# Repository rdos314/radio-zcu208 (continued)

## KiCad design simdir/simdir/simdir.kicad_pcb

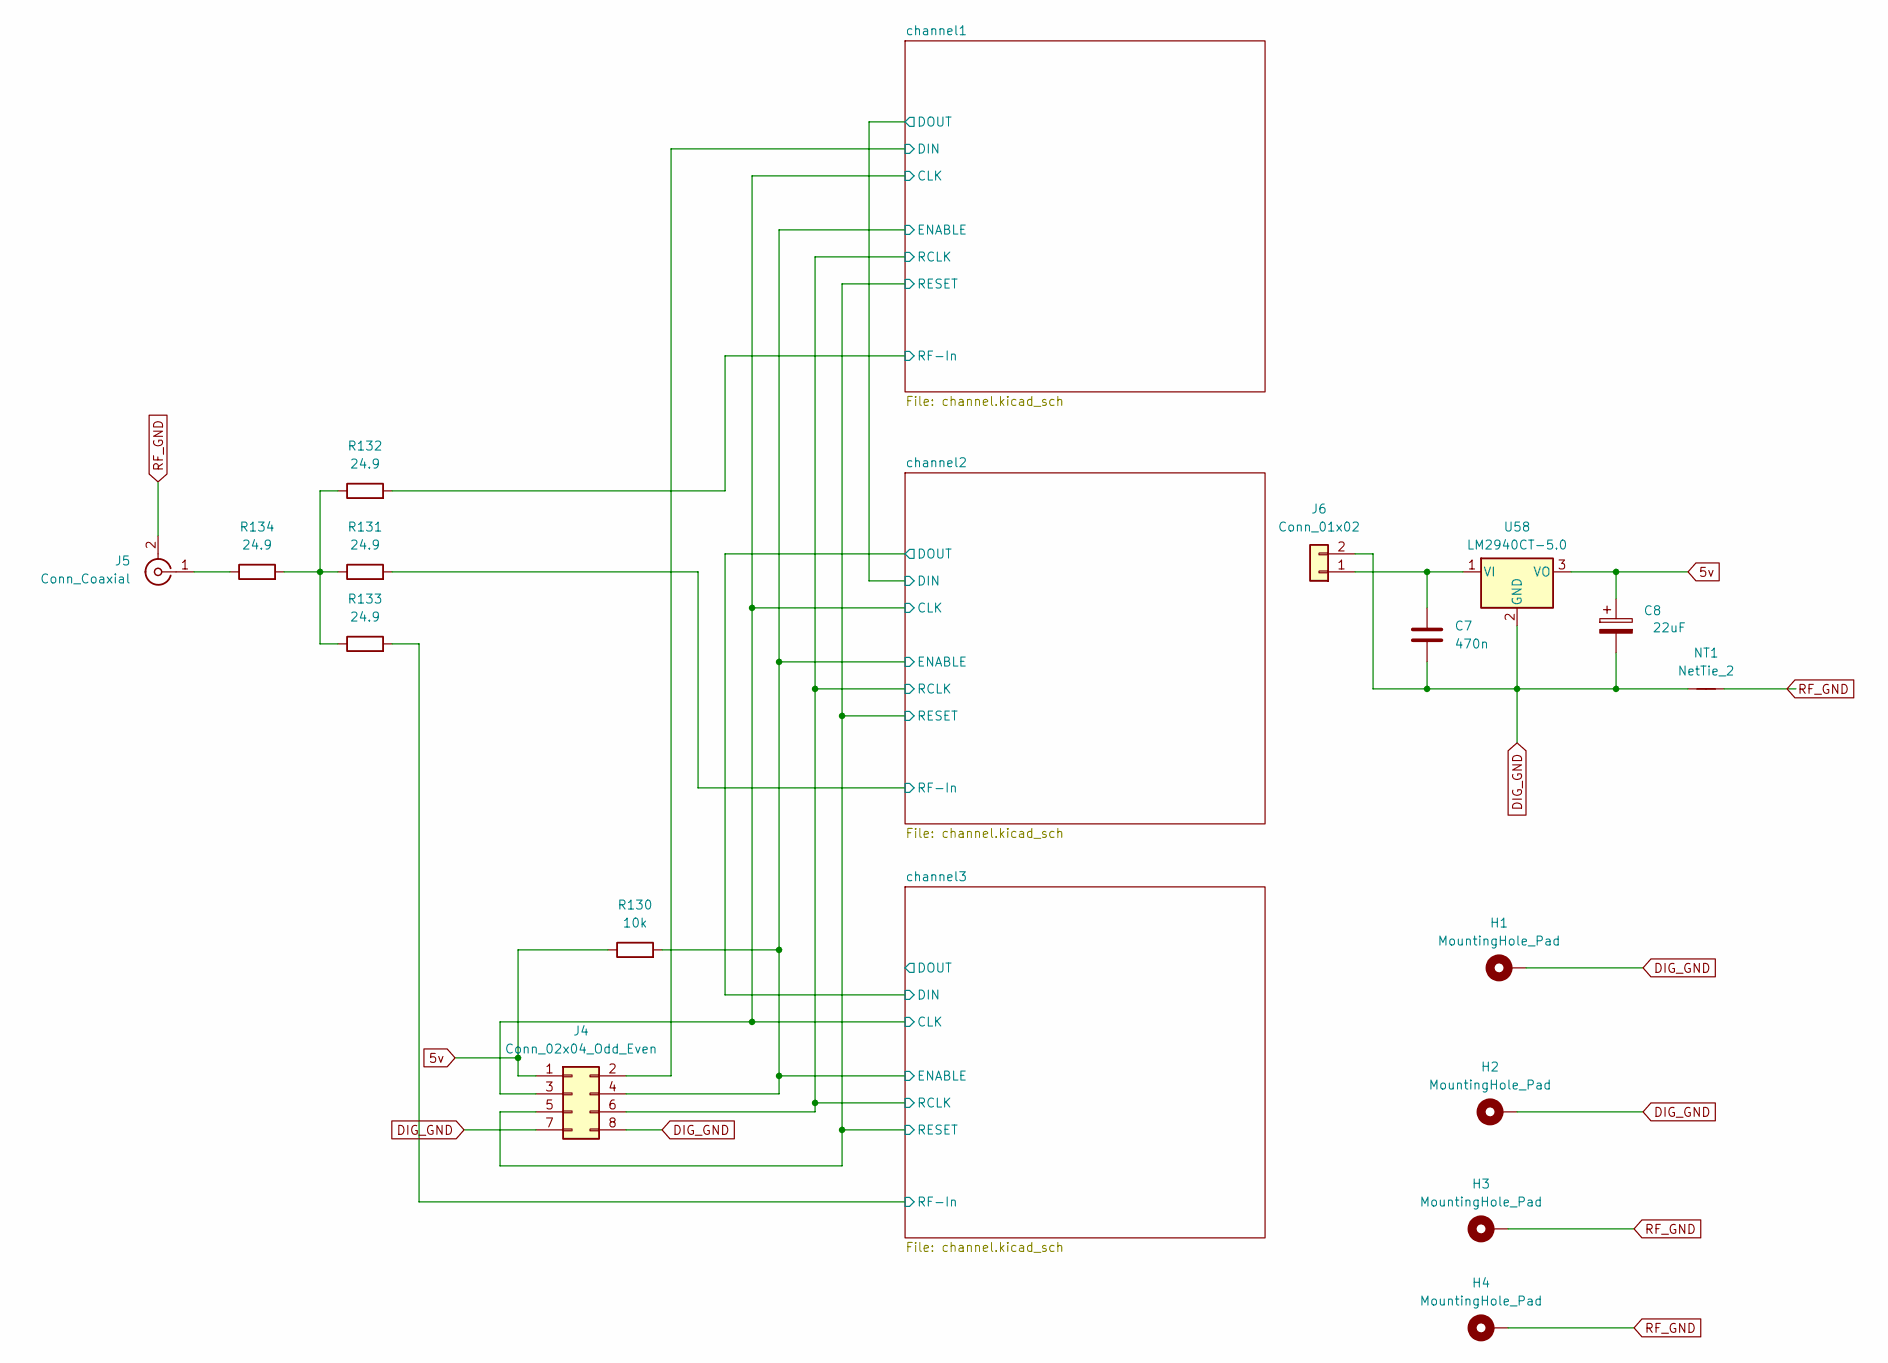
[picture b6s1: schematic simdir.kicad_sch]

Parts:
C7: 470n; C_Disc_D4.3mm_W1.9mm_P5.00mm
C8: 22uF; CP_Radial_D6.3mm_P2.50mm
H1, H2, H3, H4: MountingHole_Pad; MountingHole_4.3mm_M4_Pad_Via
J4: Conn_02x04_Odd_Even; PinHeader_2x04_P2.54mm_Vertical
J5: Conn_Coaxial; SMA_Amphenol_132289_EdgeMount
J6: Conn_01x02; PinHeader_1x02_P2.54mm_Vertical
NT1: NetTie_2; NetTie-2_THT_Pad1.0mm
R130: 10k; R_0805_2012Metric_Pad1.20x1.40mm_HandSolder
R131, R132, R133, R134: 24.9; R_0805_2012Metric_Pad1.20x1.40mm_HandSolder
U58: LM2940CT-5.0; TO-220-3_Horizontal_TabDown

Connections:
5v: C8.1, J4.1, R130.1, U58.3 (VO); also elsewhere on the board
/channel1/CLK: J4.3; also elsewhere on the board
/channel1/DIN: J4.2; also elsewhere on the board
/channel1/ENABLE: J4.4, R130.2; also elsewhere on the board
/channel1/RCLK: J4.6; also elsewhere on the board
/channel1/RESET: J4.5; also elsewhere on the board
/channel1/RF-In: R132.2; also elsewhere on the board
/channel2/RF-In: R131.2; also elsewhere on the board
/channel3/RF-In: R133.2; also elsewhere on the board
DIG_GND: C7.2, C8.2, H1.1 (1_1), H2.1 (1_1), J4.7, J4.8, J6.2, NT1.1, U58.2 (GND); also elsewhere on the board
unnamed: J5.1 (In), R134.1
unnamed: C7.1, J6.1, U58.1 (VI)
unnamed: R131.1, R132.1, R133.1, R134.2
RF_GND: H3.1 (1_1), H4.1 (1_1), J5.2 (Ext), NT1.2; also elsewhere on the board

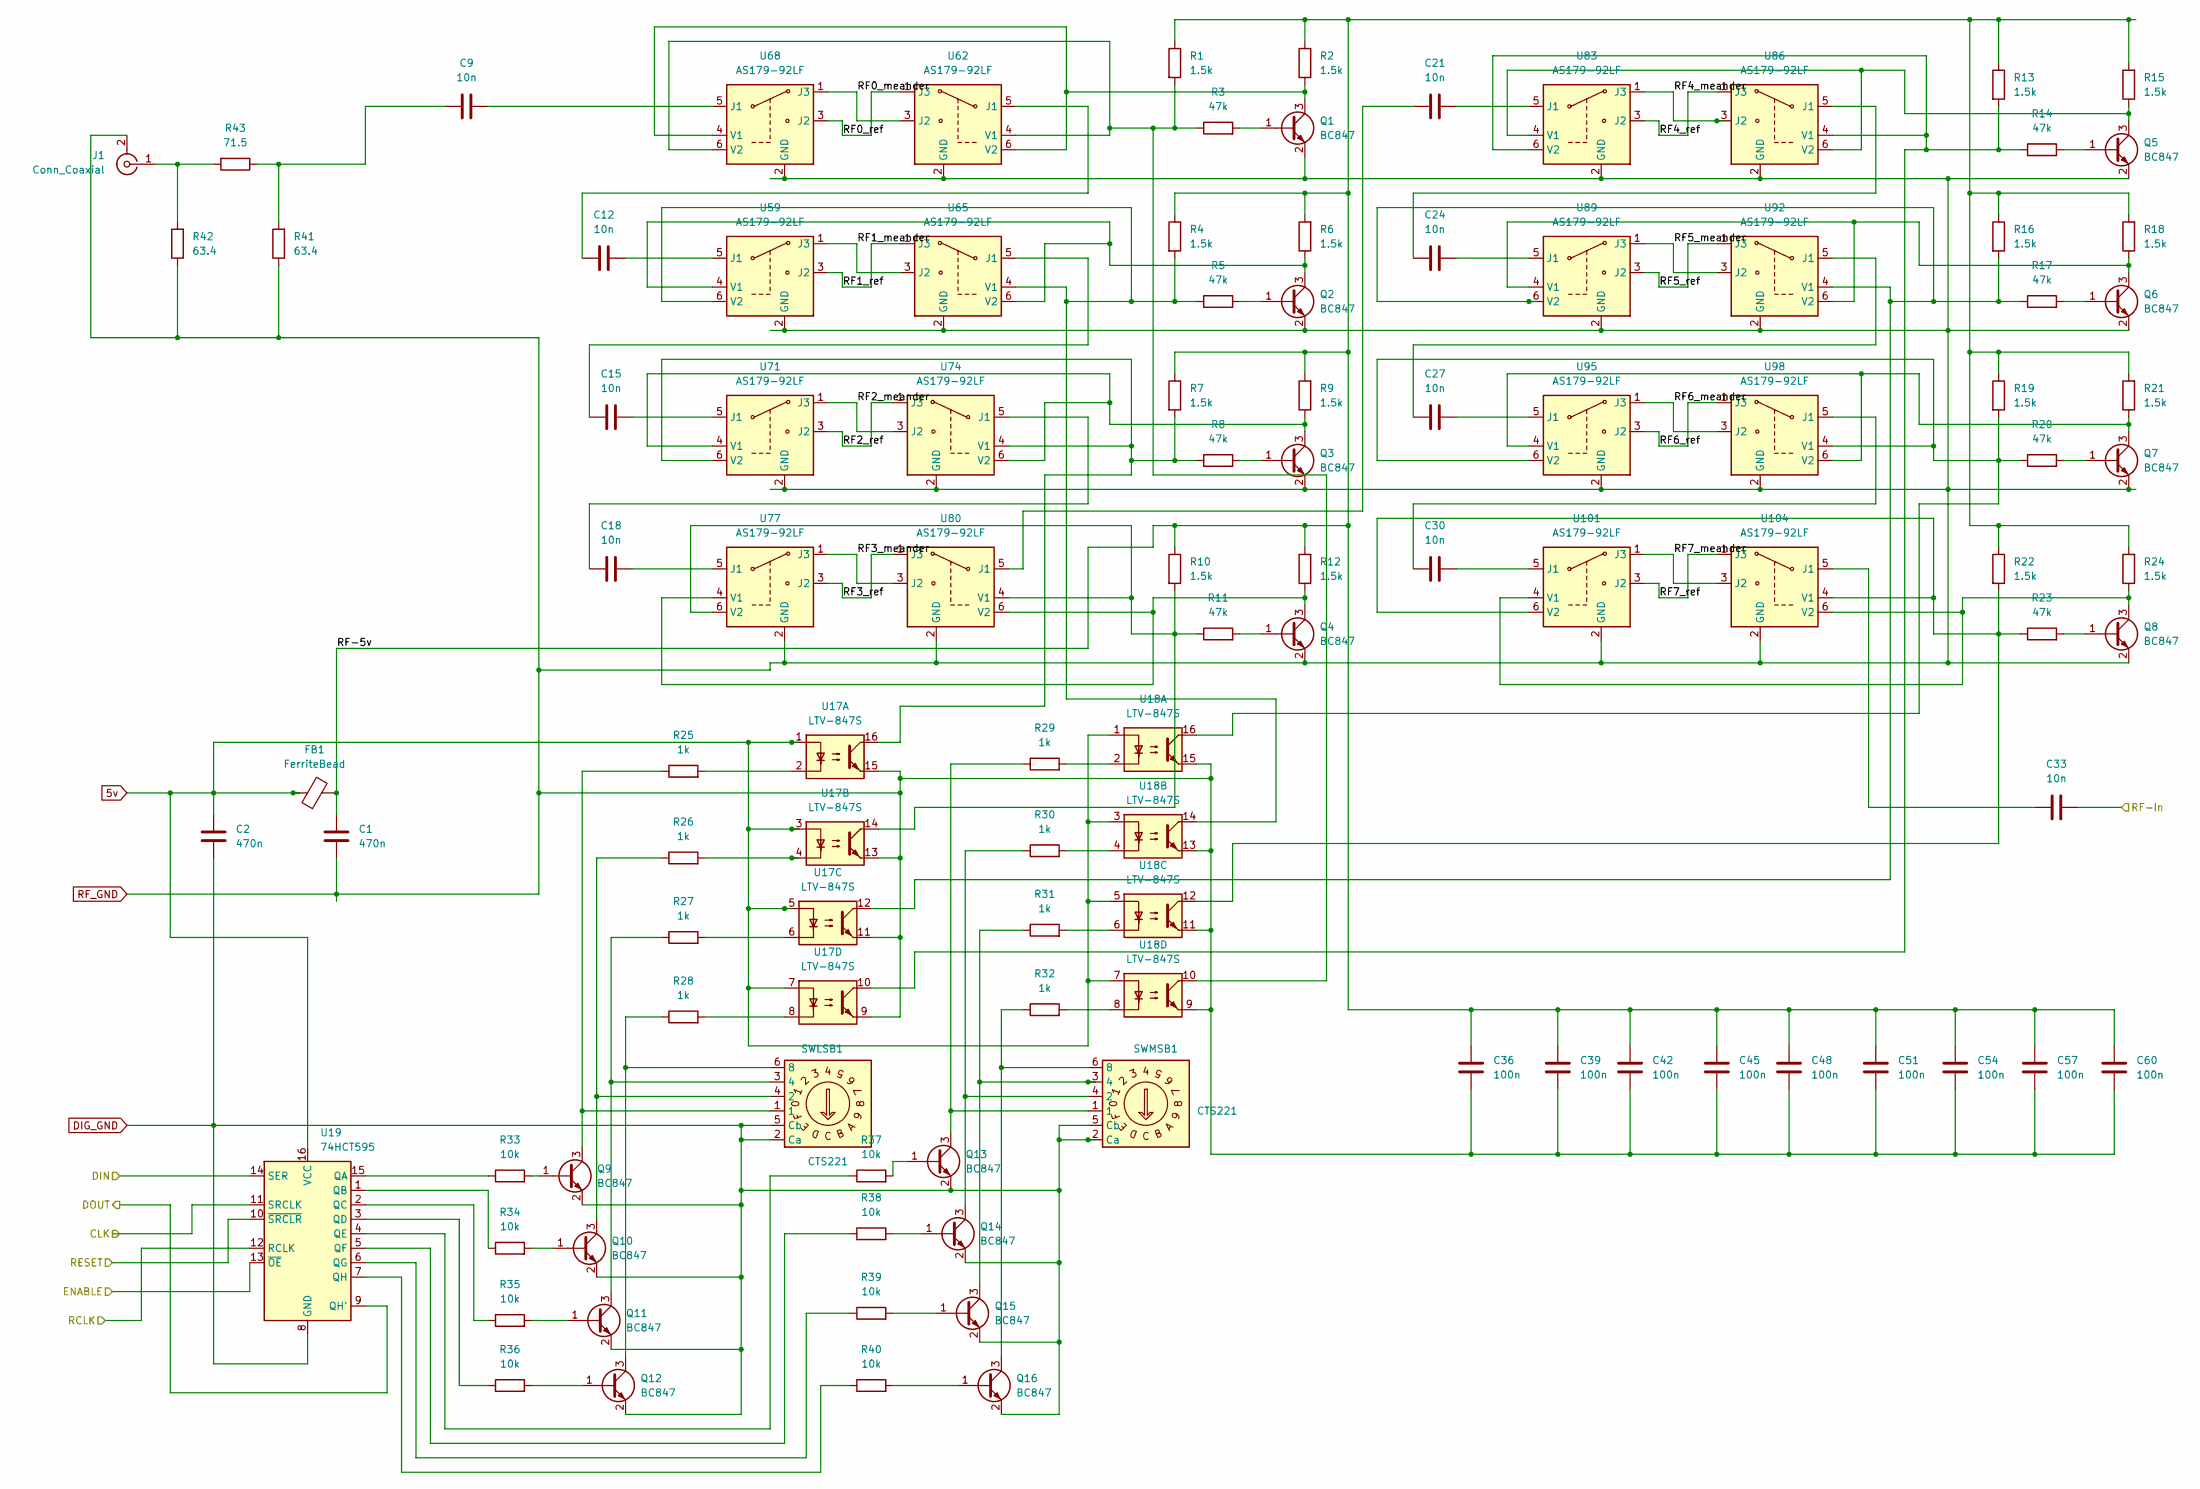
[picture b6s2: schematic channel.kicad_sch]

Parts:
C1, C2: 470n; C_0805_2012Metric_Pad1.18x1.45mm_HandSolder
C9, C12, C15, C18, C21, C24, C27, C30, C33: 10n; C_0805_2012Metric_Pad1.18x1.45mm_HandSolder
C36, C39, C42, C45, C48, C51, C54, C57, C60: 100n; C_0805_2012Metric_Pad1.18x1.45mm_HandSolder
FB1: FerriteBead; L_0805_2012Metric_Pad1.05x1.20mm_HandSolder
J1: Conn_Coaxial; SMA_Amphenol_132289_EdgeMount
Q1, Q2, Q3, Q4, Q5, Q6, Q7, Q8, Q9, Q10, Q11, Q12, Q13, Q14, Q15, Q16: BC847; SOT-23
R1, R2, R4, R6, R7, R9, R10, R12, R13, R15, R16, R18, R19, R21, R22, R24: 1.5k; R_0805_2012Metric_Pad1.20x1.40mm_HandSolder
R3, R5, R8, R11, R14, R17, R20, R23: 47k; R_0805_2012Metric_Pad1.20x1.40mm_HandSolder
R25, R26, R27, R28, R29, R30, R31, R32: 1k; R_0805_2012Metric_Pad1.20x1.40mm_HandSolder
R33, R34, R35, R36, R37, R38, R39, R40: 10k; R_0805_2012Metric_Pad1.20x1.40mm_HandSolder
R41, R42: 63.4; R_0805_2012Metric_Pad1.20x1.40mm_HandSolder
R43: 71.5; R_0805_2012Metric_Pad1.20x1.40mm_HandSolder
SWLSB1: CTS221
SWMSB1: CTS221
U17, U18: LTV-847S; SMDIP-16_W9.53mm
U19: 74HCT595; SOIC-16_3.9x9.9mm_P1.27mm
U59, U62, U65, U68, U71, U74, U77, U80, U83, U86, U89, U92, U95, U98, U101, U104: AS179-92LF; SOT-363_SC-70-6

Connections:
5v: C2.1, FB1.1, U17.1, U17.3, U17.5, U17.7, U18.1, U18.3, U18.5, U18.7, U19.16 (VCC); also elsewhere on the board
/channel1/CLK: U19.11 (SRCLK); also elsewhere on the board
/channel1/DIN: U19.14 (SER); also elsewhere on the board
/channel1/DOUT: U19.9 (QH'); also elsewhere on the board
/channel1/ENABLE: U19.13 (~OE); also elsewhere on the board
/channel1/RCLK: U19.12 (RCLK); also elsewhere on the board
/channel1/RESET: U19.10 (~SRCLR); also elsewhere on the board
/channel1/RF0_meander: U62.3 (J2), U68.1 (J3)
/channel1/RF0_ref: U62.1 (J3), U68.3 (J2)
/channel1/RF1_meander: U59.1 (J3), U65.3 (J2)
/channel1/RF1_ref: U59.3 (J2), U65.1 (J3)
/channel1/RF2_meander: U71.1 (J3), U74.3 (J2)
/channel1/RF2_ref: U71.3 (J2), U74.1 (J3)
/channel1/RF3_meander: U77.1 (J3), U80.3 (J2)
/channel1/RF3_ref: U77.3 (J2), U80.1 (J3)
/channel1/RF4_meander: U83.1 (J3), U86.3 (J2)
/channel1/RF4_ref: U83.3 (J2), U86.1 (J3)
/channel1/RF5_meander: U89.1 (J3), U92.3 (J2)
/channel1/RF5_ref: U89.3 (J2), U92.1 (J3)
/channel1/RF6_meander: U95.1 (J3), U98.3 (J2)
/channel1/RF6_ref: U95.3 (J2), U98.1 (J3)
/channel1/RF7_meander: U101.1 (J3), U104.3 (J2)
/channel1/RF7_ref: U101.3 (J2), U104.1 (J3)
/channel1/RF-5v: C1.1, C36.1, C39.1, C42.1, C45.1, C48.1, C51.1, C54.1, C57.1, C60.1, FB1.2, R1.1, R2.2, R4.1, R6.2, R7.1, R9.2, R10.1, R12.2, R13.1, R15.2, R16.1, R18.2, R19.1, R21.2, R22.1, R24.2
/channel1/RF-In: C33.2; also elsewhere on the board
DIG_GND: C2.2, Q9.2 (E), Q10.2 (E), Q11.2 (E), Q12.2 (E), Q13.2 (E), Q14.2 (E), Q15.2 (E), Q16.2 (E), SWLSB1.2 (Ca), SWLSB1.5 (Cb), SWMSB1.2 (Ca), SWMSB1.5 (Cb), U19.8 (GND); also elsewhere on the board
unnamed: C9.1, R41.2, R43.1
unnamed: J1.1 (In), R42.2, R43.2
unnamed: Q1.1 (B), R3.2
unnamed: Q1.3 (C), R2.1, U62.6 (V2), U68.4 (V1)
unnamed: Q2.1 (B), R5.2
unnamed: Q2.3 (C), R6.1, U59.4 (V1), U65.6 (V2)
unnamed: Q3.1 (B), R8.2
unnamed: Q3.3 (C), R9.1, U71.4 (V1), U74.6 (V2)
unnamed: Q4.1 (B), R11.2
unnamed: Q4.3 (C), R12.1, U77.4 (V1), U80.6 (V2)
unnamed: Q5.1 (B), R14.2
unnamed: Q5.3 (C), R15.1, U83.4 (V1), U86.6 (V2)
unnamed: Q6.1 (B), R17.2
unnamed: Q6.3 (C), R18.1, U89.4 (V1), U92.6 (V2)
unnamed: Q7.1 (B), R20.2
unnamed: Q7.3 (C), R21.1, U95.4 (V1), U98.6 (V2)
unnamed: Q8.1 (B), R23.2
unnamed: Q8.3 (C), R24.1, U101.4 (V1), U104.6 (V2)
unnamed: Q9.1 (B), R33.2
unnamed: Q9.3 (C), R25.1, SWLSB1.1
unnamed: Q10.1 (B), R34.2
unnamed: Q10.3 (C), R26.1, SWLSB1.4 (2)
unnamed: Q11.1 (B), R35.2
unnamed: Q11.3 (C), R27.1, SWLSB1.3 (4)
unnamed: Q12.1 (B), R36.2
unnamed: Q12.3 (C), R28.1, SWLSB1.6 (8)
unnamed: Q13.1 (B), R37.2
unnamed: Q13.3 (C), R29.1, SWMSB1.1
unnamed: Q14.1 (B), R38.2
unnamed: Q14.3 (C), R30.1, SWMSB1.4 (2)
unnamed: Q15.1 (B), R39.2
unnamed: Q15.3 (C), R31.1, SWMSB1.3 (4)
unnamed: Q16.1 (B), R40.2
unnamed: Q16.3 (C), R32.1, SWMSB1.6 (8)
unnamed: R25.2, U17.2
unnamed: R26.2, U17.4
unnamed: R27.2, U17.6
unnamed: R28.2, U17.8
unnamed: R29.2, U18.2
unnamed: R30.2, U18.4
unnamed: R31.2, U18.6
unnamed: R32.2, U18.8
unnamed: R33.1, U19.15 (QA)
unnamed: R34.1, U19.1 (QB)
unnamed: R35.1, U19.2 (QC)
unnamed: R36.1, U19.3 (QD)
unnamed: R37.1, U19.4 (QE)
unnamed: R38.1, U19.5 (QF)
unnamed: R39.1, U19.6 (QG)
unnamed: R40.1, U19.7 (QH)
unnamed: C12.2, U59.5 (J1)
unnamed: R4.2, R5.1, U18.14, U59.6 (V2), U65.4 (V1)
unnamed: C12.1, U62.5 (J1)
unnamed: R1.2, R3.1, U18.10, U62.4 (V1), U68.6 (V2)
unnamed: C15.1, U65.5 (J1)
unnamed: C9.2, U68.5 (J1)
unnamed: C15.2, U71.5 (J1)
unnamed: R7.2, R8.1, U17.16, U71.6 (V2), U74.4 (V1)
unnamed: C18.1, U74.5 (J1)
unnamed: C18.2, U77.5 (J1)
unnamed: R10.2, R11.1, U17.14, U77.6 (V2), U80.4 (V1)
unnamed: C21.1, U80.5 (J1)
unnamed: C21.2, U83.5 (J1)
unnamed: R13.2, R14.1, U17.10, U83.6 (V2), U86.4 (V1)
unnamed: C24.1, U86.5 (J1)
unnamed: C24.2, U89.5 (J1)
unnamed: R16.2, R17.1, U17.12, U89.6 (V2), U92.4 (V1)
unnamed: C27.1, U92.5 (J1)
unnamed: C27.2, U95.5 (J1)
unnamed: R19.2, R20.1, U18.16, U95.6 (V2), U98.4 (V1)
unnamed: C30.1, U98.5 (J1)
unnamed: C30.2, U101.5 (J1)
unnamed: R22.2, R23.1, U18.12, U101.6 (V2), U104.4 (V1)
unnamed: C33.1, U104.5 (J1)
RF_GND: C1.2, C36.2, C39.2, C42.2, C45.2, C48.2, C51.2, C54.2, C57.2, C60.2, J1.2 (Ext), Q1.2 (E), Q2.2 (E), Q3.2 (E), Q4.2 (E), Q5.2 (E), Q6.2 (E), Q7.2 (E), Q8.2 (E), R41.1, R42.1, U17.9, U17.11, U17.13, U17.15, U18.9, U18.11, U18.13, U18.15, U59.2 (GND), U62.2 (GND), U65.2 (GND), U68.2 (GND), U71.2 (GND), U74.2 (GND), U77.2 (GND), U80.2 (GND), U83.2 (GND), U86.2 (GND), U89.2 (GND), U92.2 (GND), U95.2 (GND), U98.2 (GND), U101.2 (GND), U104.2 (GND); also elsewhere on the board

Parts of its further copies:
C3, C4, C5, C6: 470n; C_0805_2012Metric_Pad1.18x1.45mm_HandSolder
C10, C11, C13, C14, C16, C17, C19, C20, C22, C23, C25, C26, C28, C29, C31, C32, C34, C35: 10n; C_0805_2012Metric_Pad1.18x1.45mm_HandSolder
C37, C38, C40, C41, C43, C44, C46, C47, C49, C50, C52, C53, C55, C56, C58, C59, C61, C62: 100n; C_0805_2012Metric_Pad1.18x1.45mm_HandSolder
FB2, FB3: FerriteBead; L_0805_2012Metric_Pad1.05x1.20mm_HandSolder
J2, J3: Conn_Coaxial; SMA_Amphenol_132289_EdgeMount
Q17, Q18, Q19, Q20, Q21, Q22, Q23, Q24, Q25, Q26, Q27, Q28, Q29, Q30, Q31, Q32, Q33, Q34, Q35, Q36, Q37, Q38, Q39, Q40, Q41, Q42, Q43, Q44, Q45, Q46, Q47, Q48: BC847; SOT-23
R44, R45, R46, R47, R52, R53, R54, R55, R87, R88, R89, R90, R95, R96, R97, R98: 10k; R_0805_2012Metric_Pad1.20x1.40mm_HandSolder
R48, R49, R50, R51, R56, R57, R58, R59, R91, R92, R93, R94, R99, R100, R101, R102: 1k; R_0805_2012Metric_Pad1.20x1.40mm_HandSolder
R60, R61, R62, R63, R68, R69, R70, R71, R72, R73, R74, R75, R83, R84, R85, R86, R103, R104, R105, R106, R111, R112, R113, R114, R115, R116, R117, R118, R126, R127, R128, R129: 1.5k; R_0805_2012Metric_Pad1.20x1.40mm_HandSolder
R64, R65, R66, R67, R77, R78, R79, R80, R107, R108, R109, R110, R120, R121, R122, R123: 47k; R_0805_2012Metric_Pad1.20x1.40mm_HandSolder
R76, R82, R119, R125: 63.4; R_0805_2012Metric_Pad1.20x1.40mm_HandSolder
R81, R124: 71.5; R_0805_2012Metric_Pad1.20x1.40mm_HandSolder
SWLSB2, SWLSB3: CTS221
SWMSB2, SWMSB3: CTS221
U20, U39: 74HCT595; SOIC-16_3.9x9.9mm_P1.27mm
U25, U30, U44, U49: LTV-847S; SMDIP-16_W9.53mm
U60, U61, U63, U64, U66, U67, U69, U70, U72, U73, U75, U76, U78, U79, U81, U82, U84, U85, U87, U88, U90, U91, U93, U94, U96, U97, U99, U100, U102, U103, U105, U106: AS179-92LF; SOT-363_SC-70-6

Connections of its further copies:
5v: C3.1, C5.1, FB2.1, FB3.1, U20.16 (VCC), U25.1, U25.3, U25.5, U25.7, U30.1, U30.3, U30.5, U30.7, U39.16 (VCC), U44.1, U44.3, U44.5, U44.7, U49.1, U49.3, U49.5, U49.7; also elsewhere on the board
/channel1/CLK: U20.11 (SRCLK), U39.11 (SRCLK); also elsewhere on the board
/channel1/DOUT: U20.14 (SER); also elsewhere on the board
/channel1/ENABLE: U20.13 (~OE), U39.13 (~OE); also elsewhere on the board
/channel1/RCLK: U20.12 (RCLK), U39.12 (RCLK); also elsewhere on the board
/channel1/RESET: U20.10 (~SRCLR), U39.10 (~SRCLR); also elsewhere on the board
/channel2/DOUT: U20.9 (QH'), U39.14 (SER)
/channel2/RF0_meander: U63.3 (J2), U69.1 (J3)
/channel2/RF0_ref: U63.1 (J3), U69.3 (J2)
/channel2/RF1_meander: U60.1 (J3), U66.3 (J2)
/channel2/RF1_ref: U60.3 (J2), U66.1 (J3)
/channel2/RF2_meander: U72.1 (J3), U75.3 (J2)
/channel2/RF2_ref: U72.3 (J2), U75.1 (J3)
/channel2/RF3_meander: U78.1 (J3), U81.3 (J2)
/channel2/RF3_ref: U78.3 (J2), U81.1 (J3)
/channel2/RF4_meander: U84.1 (J3), U87.3 (J2)
/channel2/RF4_ref: U84.3 (J2), U87.1 (J3)
/channel2/RF5_meander: U90.1 (J3), U93.3 (J2)
/channel2/RF5_ref: U90.3 (J2), U93.1 (J3)
/channel2/RF6_meander: U96.1 (J3), U99.3 (J2)
/channel2/RF6_ref: U96.3 (J2), U99.1 (J3)
/channel2/RF7_meander: U102.1 (J3), U105.3 (J2)
/channel2/RF7_ref: U102.3 (J2), U105.1 (J3)
/channel2/RF-5v: C4.1, C37.1, C40.1, C43.1, C46.1, C49.1, C52.1, C55.1, C58.1, C61.1, FB2.2, R60.1, R61.1, R62.1, R63.1, R68.2, R69.2, R70.2, R71.2, R72.1, R73.1, R74.1, R75.1, R83.2, R84.2, R85.2, R86.2
/channel2/RF-In: C34.2; also elsewhere on the board
/channel3/DOUT: U39.9 (QH')
/channel3/RF0_meander: U64.3 (J2), U70.1 (J3)
/channel3/RF0_ref: U64.1 (J3), U70.3 (J2)
/channel3/RF1_meander: U61.1 (J3), U67.3 (J2)
/channel3/RF1_ref: U61.3 (J2), U67.1 (J3)
/channel3/RF2_meander: U73.1 (J3), U76.3 (J2)
/channel3/RF2_ref: U73.3 (J2), U76.1 (J3)
/channel3/RF3_meander: U79.1 (J3), U82.3 (J2)
/channel3/RF3_ref: U79.3 (J2), U82.1 (J3)
/channel3/RF4_meander: U85.1 (J3), U88.3 (J2)
/channel3/RF4_ref: U85.3 (J2), U88.1 (J3)
/channel3/RF5_meander: U91.1 (J3), U94.3 (J2)
/channel3/RF5_ref: U91.3 (J2), U94.1 (J3)
/channel3/RF6_meander: U97.1 (J3), U100.3 (J2)
/channel3/RF6_ref: U97.3 (J2), U100.1 (J3)
/channel3/RF7_meander: U103.1 (J3), U106.3 (J2)
/channel3/RF7_ref: U103.3 (J2), U106.1 (J3)
/channel3/RF-5v: C6.1, C38.1, C41.1, C44.1, C47.1, C50.1, C53.1, C56.1, C59.1, C62.1, FB3.2, R103.1, R104.1, R105.1, R106.1, R111.2, R112.2, R113.2, R114.2, R115.1, R116.1, R117.1, R118.1, R126.2, R127.2, R128.2, R129.2
/channel3/RF-In: C35.2; also elsewhere on the board
DIG_GND: C3.2, C5.2, Q17.2 (E), Q18.2 (E), Q19.2 (E), Q20.2 (E), Q21.2 (E), Q22.2 (E), Q23.2 (E), Q24.2 (E), Q33.2 (E), Q34.2 (E), Q35.2 (E), Q36.2 (E), Q37.2 (E), Q38.2 (E), Q39.2 (E), Q40.2 (E), SWLSB2.2 (Ca), SWLSB2.5 (Cb), SWLSB3.2 (Ca), SWLSB3.5 (Cb), SWMSB2.2 (Ca), SWMSB2.5 (Cb), SWMSB3.2 (Ca), SWMSB3.5 (Cb), U20.8 (GND), U39.8 (GND); also elsewhere on the board
unnamed: C10.1, R81.1, R82.2
unnamed: C11.1, R124.1, R125.2
unnamed: J2.1 (In), R76.2, R81.2
unnamed: J3.1 (In), R119.2, R124.2
unnamed: Q17.1 (B), R44.2
unnamed: Q17.3 (C), R48.1, SWLSB2.1
unnamed: Q18.1 (B), R45.2
unnamed: Q18.3 (C), R49.1, SWLSB2.4 (2)
unnamed: Q19.1 (B), R46.2
unnamed: Q19.3 (C), R50.1, SWLSB2.3 (4)
unnamed: Q20.1 (B), R47.2
unnamed: Q20.3 (C), R51.1, SWLSB2.6 (8)
unnamed: Q21.1 (B), R52.2
unnamed: Q21.3 (C), R56.1, SWMSB2.1
unnamed: Q22.1 (B), R53.2
unnamed: Q22.3 (C), R57.1, SWMSB2.4 (2)
unnamed: Q23.1 (B), R54.2
unnamed: Q23.3 (C), R58.1, SWMSB2.3 (4)
unnamed: Q24.1 (B), R55.2
unnamed: Q24.3 (C), R59.1, SWMSB2.6 (8)
unnamed: Q25.1 (B), R64.2
unnamed: Q25.3 (C), R68.1, U63.6 (V2), U69.4 (V1)
unnamed: Q26.1 (B), R65.2
unnamed: Q26.3 (C), R69.1, U60.4 (V1), U66.6 (V2)
unnamed: Q27.1 (B), R66.2
unnamed: Q27.3 (C), R70.1, U72.4 (V1), U75.6 (V2)
unnamed: Q28.1 (B), R67.2
unnamed: Q28.3 (C), R71.1, U78.4 (V1), U81.6 (V2)
unnamed: Q29.1 (B), R77.2
unnamed: Q29.3 (C), R83.1, U84.4 (V1), U87.6 (V2)
unnamed: Q30.1 (B), R78.2
unnamed: Q30.3 (C), R84.1, U90.4 (V1), U93.6 (V2)
unnamed: Q31.1 (B), R79.2
unnamed: Q31.3 (C), R85.1, U96.4 (V1), U99.6 (V2)
unnamed: Q32.1 (B), R80.2
unnamed: Q32.3 (C), R86.1, U102.4 (V1), U105.6 (V2)
unnamed: Q33.1 (B), R87.2
unnamed: Q33.3 (C), R91.1, SWLSB3.1
unnamed: Q34.1 (B), R88.2
unnamed: Q34.3 (C), R92.1, SWLSB3.4 (2)
unnamed: Q35.1 (B), R89.2
unnamed: Q35.3 (C), R93.1, SWLSB3.3 (4)
unnamed: Q36.1 (B), R90.2
unnamed: Q36.3 (C), R94.1, SWLSB3.6 (8)
unnamed: Q37.1 (B), R95.2
unnamed: Q37.3 (C), R99.1, SWMSB3.1
unnamed: Q38.1 (B), R96.2
unnamed: Q38.3 (C), R100.1, SWMSB3.4 (2)
unnamed: Q39.1 (B), R97.2
unnamed: Q39.3 (C), R101.1, SWMSB3.3 (4)
unnamed: Q40.1 (B), R98.2
unnamed: Q40.3 (C), R102.1, SWMSB3.6 (8)
unnamed: Q41.1 (B), R107.2
unnamed: Q41.3 (C), R111.1, U64.6 (V2), U70.4 (V1)
unnamed: Q42.1 (B), R108.2
unnamed: Q42.3 (C), R112.1, U61.4 (V1), U67.6 (V2)
unnamed: Q43.1 (B), R109.2
unnamed: Q43.3 (C), R113.1, U73.4 (V1), U76.6 (V2)
unnamed: Q44.1 (B), R110.2
unnamed: Q44.3 (C), R114.1, U79.4 (V1), U82.6 (V2)
unnamed: Q45.1 (B), R120.2
unnamed: Q45.3 (C), R126.1, U85.4 (V1), U88.6 (V2)
unnamed: Q46.1 (B), R121.2
unnamed: Q46.3 (C), R127.1, U91.4 (V1), U94.6 (V2)
unnamed: Q47.1 (B), R122.2
unnamed: Q47.3 (C), R128.1, U97.4 (V1), U100.6 (V2)
unnamed: Q48.1 (B), R123.2
unnamed: Q48.3 (C), R129.1, U103.4 (V1), U106.6 (V2)
unnamed: R48.2, U25.2
unnamed: R49.2, U25.4
unnamed: R50.2, U25.6
unnamed: R51.2, U25.8
unnamed: R56.2, U30.2
unnamed: R57.2, U30.4
unnamed: R58.2, U30.6
unnamed: R59.2, U30.8
unnamed: R91.2, U44.2
unnamed: R92.2, U44.4
unnamed: R93.2, U44.6
unnamed: R94.2, U44.8
unnamed: R99.2, U49.2
unnamed: R100.2, U49.4
unnamed: R101.2, U49.6
unnamed: R102.2, U49.8
unnamed: R44.1, U20.15 (QA)
unnamed: R45.1, U20.1 (QB)
unnamed: R46.1, U20.2 (QC)
unnamed: R47.1, U20.3 (QD)
unnamed: R52.1, U20.4 (QE)
unnamed: R53.1, U20.5 (QF)
unnamed: R54.1, U20.6 (QG)
unnamed: R55.1, U20.7 (QH)
unnamed: R87.1, U39.15 (QA)
unnamed: R88.1, U39.1 (QB)
unnamed: R89.1, U39.2 (QC)
unnamed: R90.1, U39.3 (QD)
unnamed: R95.1, U39.4 (QE)
unnamed: R96.1, U39.5 (QF)
unnamed: R97.1, U39.6 (QG)
unnamed: R98.1, U39.7 (QH)
unnamed: C13.2, U60.5 (J1)
unnamed: R61.2, R65.1, U30.14, U60.6 (V2), U66.4 (V1)
unnamed: C14.2, U61.5 (J1)
unnamed: R104.2, R108.1, U49.14, U61.6 (V2), U67.4 (V1)
unnamed: C13.1, U63.5 (J1)
unnamed: R60.2, R64.1, U30.10, U63.4 (V1), U69.6 (V2)
unnamed: C14.1, U64.5 (J1)
unnamed: R103.2, R107.1, U49.10, U64.4 (V1), U70.6 (V2)
unnamed: C16.1, U66.5 (J1)
unnamed: C17.1, U67.5 (J1)
unnamed: C10.2, U69.5 (J1)
unnamed: C11.2, U70.5 (J1)
unnamed: C16.2, U72.5 (J1)
unnamed: R62.2, R66.1, U25.16, U72.6 (V2), U75.4 (V1)
unnamed: C17.2, U73.5 (J1)
unnamed: R105.2, R109.1, U44.16, U73.6 (V2), U76.4 (V1)
unnamed: C19.1, U75.5 (J1)
unnamed: C20.1, U76.5 (J1)
unnamed: C19.2, U78.5 (J1)
unnamed: R63.2, R67.1, U25.14, U78.6 (V2), U81.4 (V1)
unnamed: C20.2, U79.5 (J1)
unnamed: R106.2, R110.1, U44.14, U79.6 (V2), U82.4 (V1)
unnamed: C22.1, U81.5 (J1)
unnamed: C23.1, U82.5 (J1)
unnamed: C22.2, U84.5 (J1)
unnamed: R72.2, R77.1, U25.10, U84.6 (V2), U87.4 (V1)
unnamed: C23.2, U85.5 (J1)
unnamed: R115.2, R120.1, U44.10, U85.6 (V2), U88.4 (V1)
unnamed: C25.1, U87.5 (J1)
unnamed: C26.1, U88.5 (J1)
unnamed: C25.2, U90.5 (J1)
unnamed: R73.2, R78.1, U25.12, U90.6 (V2), U93.4 (V1)
unnamed: C26.2, U91.5 (J1)
unnamed: R116.2, R121.1, U44.12, U91.6 (V2), U94.4 (V1)
unnamed: C28.1, U93.5 (J1)
unnamed: C29.1, U94.5 (J1)
unnamed: C28.2, U96.5 (J1)
unnamed: R74.2, R79.1, U30.16, U96.6 (V2), U99.4 (V1)
unnamed: C29.2, U97.5 (J1)
unnamed: C31.1, U99.5 (J1)
unnamed: C32.1, U100.5 (J1)
unnamed: R117.2, R122.1, U49.16, U97.6 (V2), U100.4 (V1)
unnamed: C31.2, U102.5 (J1)
unnamed: R75.2, R80.1, U30.12, U102.6 (V2), U105.4 (V1)
unnamed: C32.2, U103.5 (J1)
unnamed: R118.2, R123.1, U49.12, U103.6 (V2), U106.4 (V1)
unnamed: C34.1, U105.5 (J1)
unnamed: C35.1, U106.5 (J1)
RF_GND: C4.2, C6.2, C37.2, C38.2, C40.2, C41.2, C43.2, C44.2, C46.2, C47.2, C49.2, C50.2, C52.2, C53.2, C55.2, C56.2, C58.2, C59.2, C61.2, C62.2, J2.2 (Ext), J3.2 (Ext), Q25.2 (E), Q26.2 (E), Q27.2 (E), Q28.2 (E), Q29.2 (E), Q30.2 (E), Q31.2 (E), Q32.2 (E), Q41.2 (E), Q42.2 (E), Q43.2 (E), Q44.2 (E), Q45.2 (E), Q46.2 (E), Q47.2 (E), Q48.2 (E), R76.1, R82.1, R119.1, R125.1, U25.9, U25.11, U25.13, U25.15, U30.9, U30.11, U30.13, U30.15, U44.9, U44.11, U44.13, U44.15, U49.9, U49.11, U49.13, U49.15, U60.2 (GND), U61.2 (GND), U63.2 (GND), U64.2 (GND), U66.2 (GND), U67.2 (GND), U69.2 (GND), U70.2 (GND), U72.2 (GND), U73.2 (GND), U75.2 (GND), U76.2 (GND), U78.2 (GND), U79.2 (GND), U81.2 (GND), U82.2 (GND), U84.2 (GND), U85.2 (GND), U87.2 (GND), U88.2 (GND), U90.2 (GND), U91.2 (GND), U93.2 (GND), U94.2 (GND), U96.2 (GND), U97.2 (GND), U99.2 (GND), U100.2 (GND), U102.2 (GND), U103.2 (GND), U105.2 (GND), U106.2 (GND); also elsewhere on the board

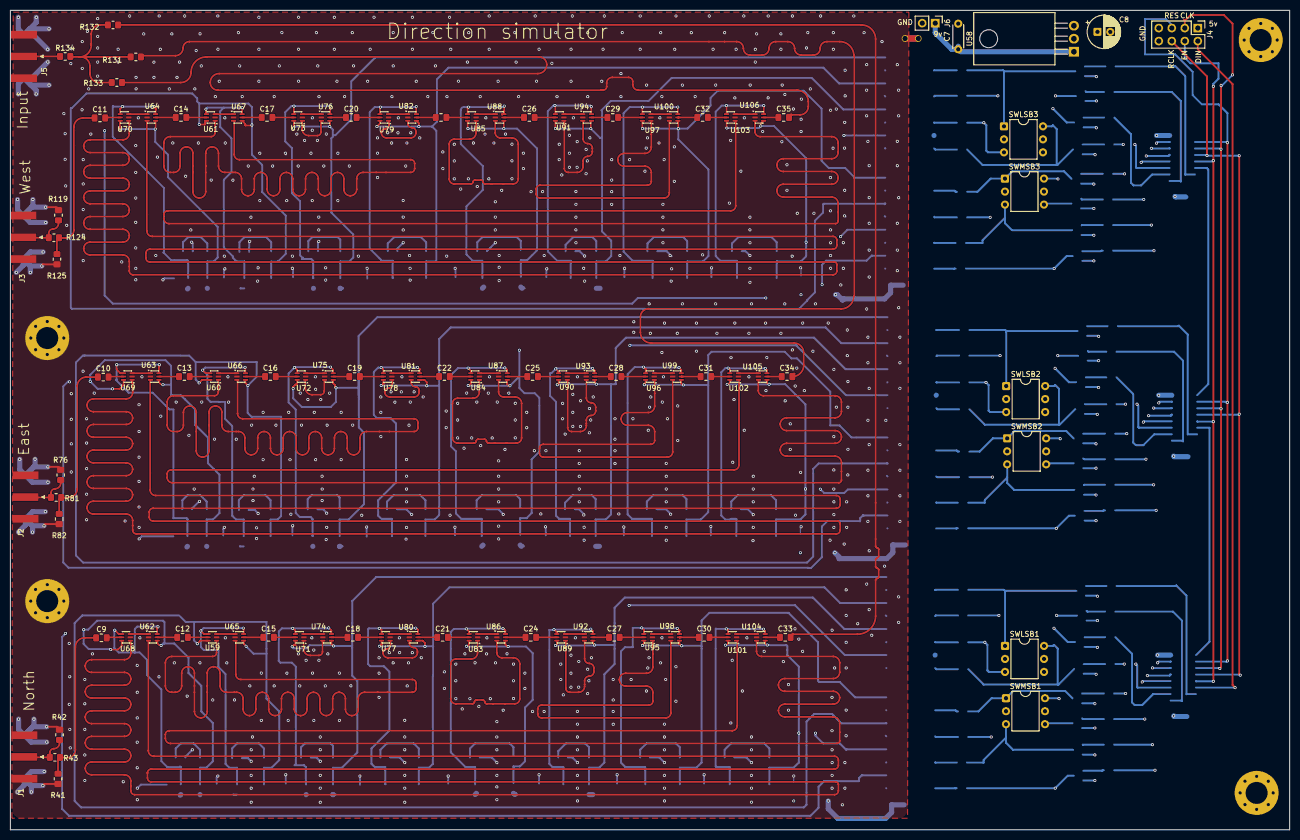
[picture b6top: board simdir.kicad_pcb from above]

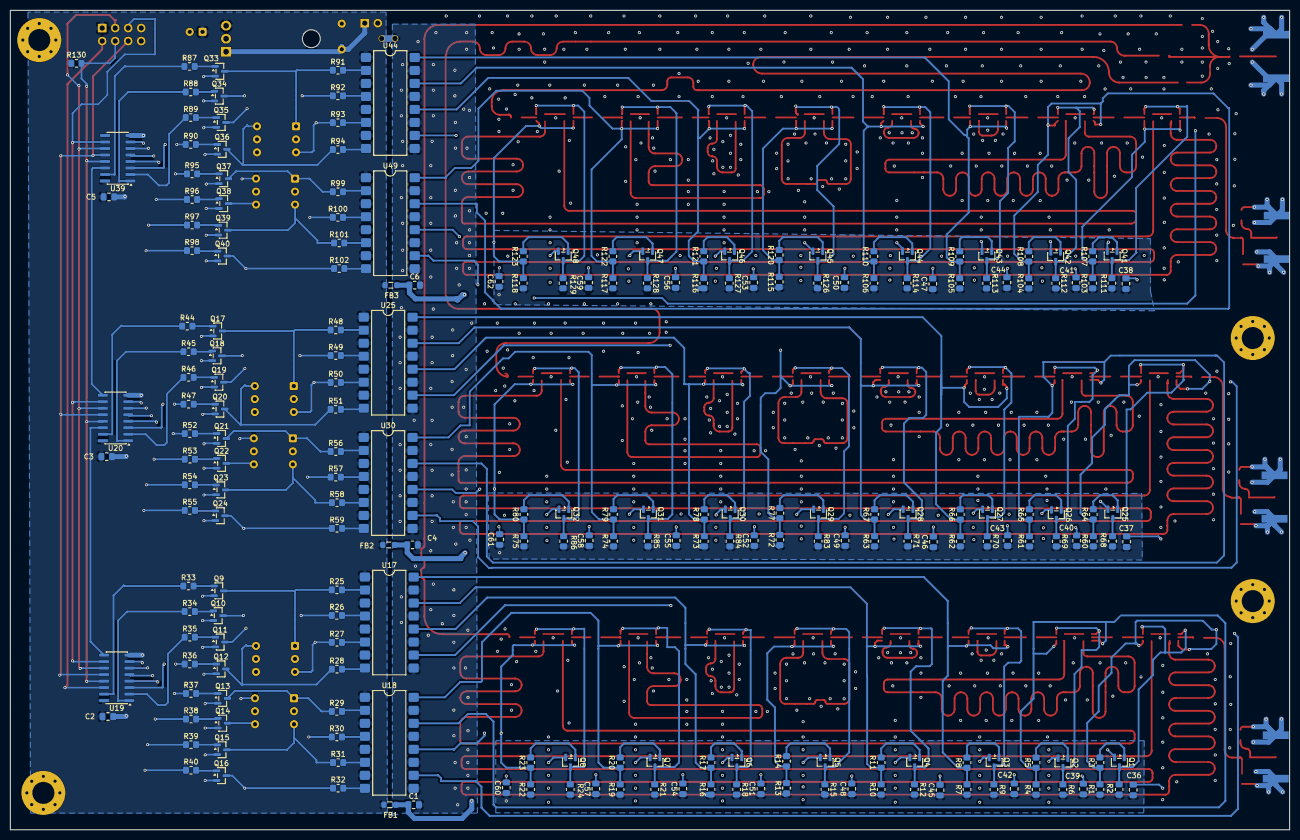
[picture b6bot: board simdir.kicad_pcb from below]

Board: 4 copper layers, 249.9 x 160.1 mm, 322 parts (214 on the bottom side), 289 nets.

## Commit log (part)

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2025-09-12 Remote debugging, SFTP and apache2 added
2025-09-12 Added boot configuration (bif file) for Vitis.
2025-09-12 Added SDK to Vitis
2025-09-12 Added Linux analysis app.
2025-09-20 Added Vivado
2025-09-20 Added Vitis.
2025-09-20 Added petalinux
2025-09-20 Export correct file.
2025-09-20 Add Vitis Linux build.
2025-09-20 Modified include files.
2025-09-20 Added debug settings.
2025-09-21 Add dummy app
2025-09-21 Rebuilt Linux
2025-09-21 Setup correct Linux debug.
2025-09-21 Updated ignored.
2025-09-21 Try to ignore ide changes
2025-09-21 Removed PMU and FSBL from platform.
2025-09-21 Added PMU and FSBL as separate projects.
2025-09-21 Added default bif without Linux.
2025-09-21 Added PL clk.
2025-09-21 Added generated files.
2025-09-21 Fixed PL-0 clock problem.
2025-09-21 Seems like the fix is reverted somehow.
2025-09-21 Some useless changes.
2025-09-22 Removed non-needed files.
2025-09-22 Added custom fstab.
2025-09-22 Fixed so LEDs work in control app.
2025-09-23 Added maridb and phpmyadmin.
2025-09-26 Added CLK104 code.
2025-09-26 Add stdbool.h
2025-09-26 Fixed project files.
2025-09-26 Recreated xsa, but CLK104 initialization still doesn't work and the GPIO code crashes with Linux.
2025-09-28 Added CLK104 mux. Fixed setup-code of CLK104.
2025-09-29 Removed cache.
2025-09-29 Moved clk104 functionality into single file.
2025-09-29 Reorder and remove unnecessary parameters.
2025-09-29 Remove /.cache.
2025-09-29 Improved config & readout to single round. Remove unneeded functions.
2025-09-29 Fix bug.
2025-09-29 Removed irrelevant LMK & LMX entries.
2025-09-30 Removed lots of junk from control app.
2025-09-30 Added RFDC component.
2025-10-01 Added ILAs
2025-10-01 Added MTS code + changed ILA interface.
2025-10-01 Added constraints for pl_clk and pl_sysref from CLK104 board.
2025-10-01 Add more detect code for MTS and tiles.
2025-10-01 Doesn't build but still has improved MTS.
2025-10-02 Provided the correct MTS SYSREF interface from PG269.
2025-10-02 Updated mts for better functionality.
2025-10-02 Builds but has timing errors because of false paths.
2025-10-03 Added changes.
2025-10-03 More updates..
2025-10-03 Builds without timing errors.
2025-10-04 Fixed control app.
2025-10-06 Added 2.5 G sample rate to control app.
2025-10-06 Added 3G option too.
2025-10-06 Update modules to support several lengths more easily.
2025-10-06 The last two tiles now startup at 5GHz.
2025-10-07 Working 5 GHz ADC on six channels + working MTS.
2025-10-28 Updated platform
2025-11-01 Fixed timing errors and clock domain interaction.
2025-11-02 Changed doa decimate.v and add FIFO interface.
2025-11-02 Added composite module and connect to raw FIFO.
2025-11-02 Added FIR decimation filters.
2025-11-03 Setup real FIR decimation filters.
2025-11-04 Moved FIR filter inside Verilog code.
2025-11-05 Added Complex Morlet calculation code.
2025-11-05 Added sampling frequency to Mortlet generation.
2025-11-07 Moved FIFO inside module. Modified decimation filters.
2025-11-08 Added decimate by two for low frequency raw data,
2025-11-10 Changed CLK104 config to 4 GHz.
2025-11-12 Added 4 GHz register export
2025-11-12 Added new 4 GHz table entry.
2025-11-12 Change SYSREF to be similar to 3 and 5 GHz modes.
2025-11-12 Changed to 4 GHz sampling frequency.
2025-11-13 Added DoA FIFOs.
2025-11-15 Added complex Morlet wavelets for DoA.
2025-11-15 Added converter to phase and envelope.
2025-11-16 Average all three low-frequency channels.
2025-11-20 Redo the Vivado part.
2025-11-20 Added MUX to decimation.
2025-11-21 Sim loading almost works, but address lines appears to be misaligned.
2025-11-21 Working BRAM except R5 readback which should be single cycle.
2025-11-22 Simulation transfer works, but repeats indefinitely.
2025-11-22 Works a bit better but still has issues.
2025-11-23 Sim logic ok.
2025-11-23 Simulation works up to reading out deci FIFOs.
2025-11-24 Modified start & stop logic.
2025-11-24 Simulation is broken
2025-11-25 Output of simulation perfectly aligned.
2025-11-26 Low freq raw decimation works and is aligned.
2025-11-26 Whole low deci chain works.
2025-11-27 Deci part works.
2025-11-28 Fixed minor issues.
2025-11-29 Fixes for read-out, but still not ok.
2025-11-30 DoA path mostly works, but raw path needs more correction for proper timing.
2025-11-30 Raw and DoA sequencies correctly aligned for both low and high frequencies.
2025-11-30 Renamed doa to freq.
2025-12-02 Setup for debugging Morlet converter.
2025-12-03 Improved Morlet handling.
2025-12-03 Low Morlet works.
2025-12-09 Correct alignment of DoA input for 46 MHz
2025-12-11 Moved FIFO to freq part.
2025-12-11 Low channel works up to DoA, but high channel doesn't start.
2025-12-13 High channel starts + test app modified for direction.
2025-12-14 Added error values for direction.
2025-12-15 Signals input to composite FIFOs are aligned and correct.
2025-12-15 Removed redundant ILAs.
2025-12-17 Config parameters added.
2025-12-19 Implemented config settings in comp.
2025-12-19 Added signal detection.
2025-12-20 Weighted sum of delta-phase x env using DSP slice added.
2025-12-21 Average phase differences work.
2025-12-22 Working frequency & phase calculation.
2025-12-22 Average envelopes ok, DoA logic added but not working.
2025-12-23 Working arcsin using Taylor series.
2025-12-25 Fixed scaling and boarder cases.
2025-12-26 Added AI comment, removed irrelevant ILAs and changed done to 1 cycle.
2025-12-27 Switched to WN to use a proper order.
2025-12-28 Compass angle works.
2025-12-31 Added delay implementation, but doesn't work properly.
2025-12-31 Delay calculations are correct.
2026-01-01 Added composite generators.
2026-01-01 Reduced angles to 16 bits.
2026-01-01 Added sample factor & calculate sample distance.
2026-01-03 Calculated phase is correct & fixed pipelines.
2026-01-04 Phase error determination works.
2026-01-06 Calculate antenna geometry error in promille instead of in meter.
2026-01-06 DoA stage works except for composite values and size.
2026-01-06 Size and composite offsets correct.
2026-01-07 Changed to ana* and removed sample data input.
2026-01-07 Remove raw data from freq*.
2026-01-09 Used better module interfaces.
2026-01-09 Removed average env (not used).
2026-01-10 Used same ana module.
2026-01-10 Added raw modules.
2026-01-10 Added composite modules.
2026-01-10 Removed unused components.
2026-01-10 Created composite signal.
2026-01-11 Morlet wavelet works with decimation with two.
2026-01-13 Fixed sample triggers.
2026-01-13 Added composite analysis module.
2026-01-15 Fixed some errors, but fails timing closure.
2026-01-16 Fixed minor issues, ILA results in massive timing failure.
2026-01-18 Reduced samples to 16 bits.
2026-01-19 Added ILA to find composite align error.
2026-01-21 Multicycle start fixed, but fails timing due to complexity.
2026-01-22 Composite signal is correct.
2026-01-23 Updated FIRs, but the gain is still not correct.
2026-01-23 Composite envelope set to 95% of input signal.
2026-01-23 Update freq Morlet with new paramaters.
2026-01-26 Perfect alignment for both frequency bands.
2026-01-27 Added logic for burst length detection (not yet working).
2026-01-29 Length calculation works.
2026-01-29 Aligned data written back.
2026-01-31 Prepared for four stages in the final processing.
2026-02-03 Added frequency error predictor (not working).,
2026-02-04 Frequency update & statistics data series now work.
2026-02-05 Reworked composite stage (non-working)
2026-02-06 New clock distribution works, but has minor bugs.
2026-02-06 New design works.
2026-02-07 Approximate mean calculation works.
2026-02-08 Flow control works, but isses with timing closure.
2026-02-15 A working version that might need IDR for timing closure.
2026-02-15 Basics for sum & squared sum for standard deviation.
2026-02-15 Added 24 bit multiplier and 48 bit divider.
2026-02-17 Statistics output align, but last four samples are incorrect (repeated).
2026-02-18 Correct sample alignment.
2026-02-18 Added phase 4, but not working.
2026-02-20 Major refactory of statistics calculations.
2026-02-20 Refactoring of control mechanism.
2026-02-22 Frequency compensation works.
2026-02-22 Statistics module works.
2026-02-23 Stage four completed, but not fully tested.
2026-02-23 Goes a bit longer, but size not set.
2026-02-23 Split the size step + fixed some bugs in the forth.
2026-03-01 Added single PL DDR4 (MIG).
2026-03-01 Updated Linux image.
2026-03-04 Added AXI module.
2026-03-05 Improved AXI, but not yet fully functional.
2026-03-06 MIG AXI works.
2026-03-06 Added comp AXI, but not yet fully functional.
2026-03-07 Improved comp AXI.
2026-03-09 Based on IDR.
2026-03-09 All stat data come out correctly, but read_back active two cycles.
2026-03-10 One cycle read-back, but one dataset still missing.
2026-03-10 Added burst output FIFO.
2026-03-12 Improved FIFO function, but not quite right.
2026-03-13 AXI data still comes out one cycle too late.
2026-03-13 AXI data now aligned.
2026-03-14 Pulses on three channels appear to work.
2026-03-16 Added seven stat modules.
2026-03-18 Stat module mixing works.
2026-03-28 Moved to Linux platform
2026-03-28 Added petalinux SDK
2026-03-28 Modified MIG map.
2026-03-28 Added no-map
2026-03-28 Rebuild Linux
2026-03-28 Working mapping of MIG in Linux app.
2026-03-30 Preparing to save in URAM (low header is incorrect).
2026-04-01 AXI works but has one package too little.
2026-04-03 Added URAM FIFO to AXI
2026-04-05 Correct raw data provided.
2026-04-06 Band merge added, but not fully functional.
2026-04-08 Band merge works.
2026-04-08 Added final URAM FIFO.
2026-04-10 Improved Linux app
2026-04-10 Fixed MIG interface
2026-04-12 Output to Linux is correct.
2026-04-12 Remove changing files
2026-04-12 Auto stash before merge of "main" and "origin/main"
    Added analyser fixes.
2026-04-13 Added reserved region.
2026-04-13 Added description.
2026-04-15 Added ptr FIFOs and AXI component.
2026-04-15 Separated read & write pointers into two ports.
2026-04-20 Add axi lite spy IP.
2026-04-21 Updated AXI modules.
2026-04-22 Added ILAs for test.
2026-04-26 FIFO is read one cycle too long.
2026-04-27 Fixed size & idle bugs.
2026-04-27 Code works up to pad.
2026-04-29 Pad stiill misbehaves.
2026-04-29 This should fix pad issue.
2026-04-29 Padding works.
2026-04-29 Added gdbserver and axidma driver.
2026-04-29 Updated kernel driver and system dtsi.
2026-04-30 Fixed device-driver and dtsi problems.
2026-04-30 Auto stash before merge of "main" and "origin/main"
2026-04-30 Updated platform + fixed kernel driver so it builds.
2026-04-30 Use IRQ instead of IPI.
2026-04-30 Update driver.
2026-05-01 Linux driver now registers interrupt 53.
2026-05-01 Added AXI interrupt controller
2026-05-01 Working Linux device driver that handles PL interrupts.
2026-05-03 Fixed wrong RESET polarity
2026-05-03 Add pad support to Linux app. Test axidma device.
2026-05-03 Add pad support to Linux app. Test axidma device
2026-05-04 Test for Linux pointers.
2026-05-04 Updated MIG read-out.
2026-05-04 Fix minor issue.
2026-05-04 Fixed some MIG reader bugs.
2026-05-05 MIG reader no longer overflow, but saves too much data into FIFO
2026-05-06 MIG reader works, and outputs correct entries to FIFO.
2026-05-06 Changes to adc test.
2026-05-06 Added CLion project for analyzer.
2026-05-07 Add Linux writer basics.
2026-05-07 Commit changes.-
2026-05-07 Fixed race condition in Linux writer.
2026-05-11 Linux writer works first time.
2026-05-12 Improved Linux side burst handling.
2026-05-12 Linux writer works (no TLAST or TKEEP).
2026-05-12 Updated SDK
2026-05-13 Remove netfilter
2026-05-13 Remove rest of netfilter.
2026-05-13 Fixed so CLion should use the correct cross-compiler.
2026-05-14 Linux writer works, but last beat is repeated.
2026-05-15 Fixed duplicated bug & enabled read ADC.
2026-05-15 Start ADC and disable printing raw data.
2026-05-16 Real ADC works but angle is wrong.
2026-05-17 Fixed angle calculation & tuned config parameters.
2026-05-17 Log amplitudes again.
2026-05-18 Set DSA to avoid spurious overload.
2026-05-18 Set DSA to 9 dB to preserve dynamic range.
2026-05-31 Increased high freq comp size to 11 periods.
2026-05-31 Updated decimation filters.
2026-06-01 Shortened freq filter to approx 250 ns.
